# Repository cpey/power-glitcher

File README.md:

# Power Glitcher

Power glitcher circuit for voltage fault injection. Similar to [1], it includes
a DAC, a non-inverting amplification stage, and a push-pull follower output
circuit.

The board can function as ON/OFF switch, bypassing the DAC, by connecting a GPIO
output to the J5 connector and short-circuiting JP1. Refer to the
[schematic](https://github.com/cpey/power-glitcher/blob/main/power_glitcher/power_glitcher.pdf)
for more details.

[1] D. Oswald, *A Versatile Framework for Implementation Attacks on Cryptographic RFIDs and Embedded Devices*, 2010.

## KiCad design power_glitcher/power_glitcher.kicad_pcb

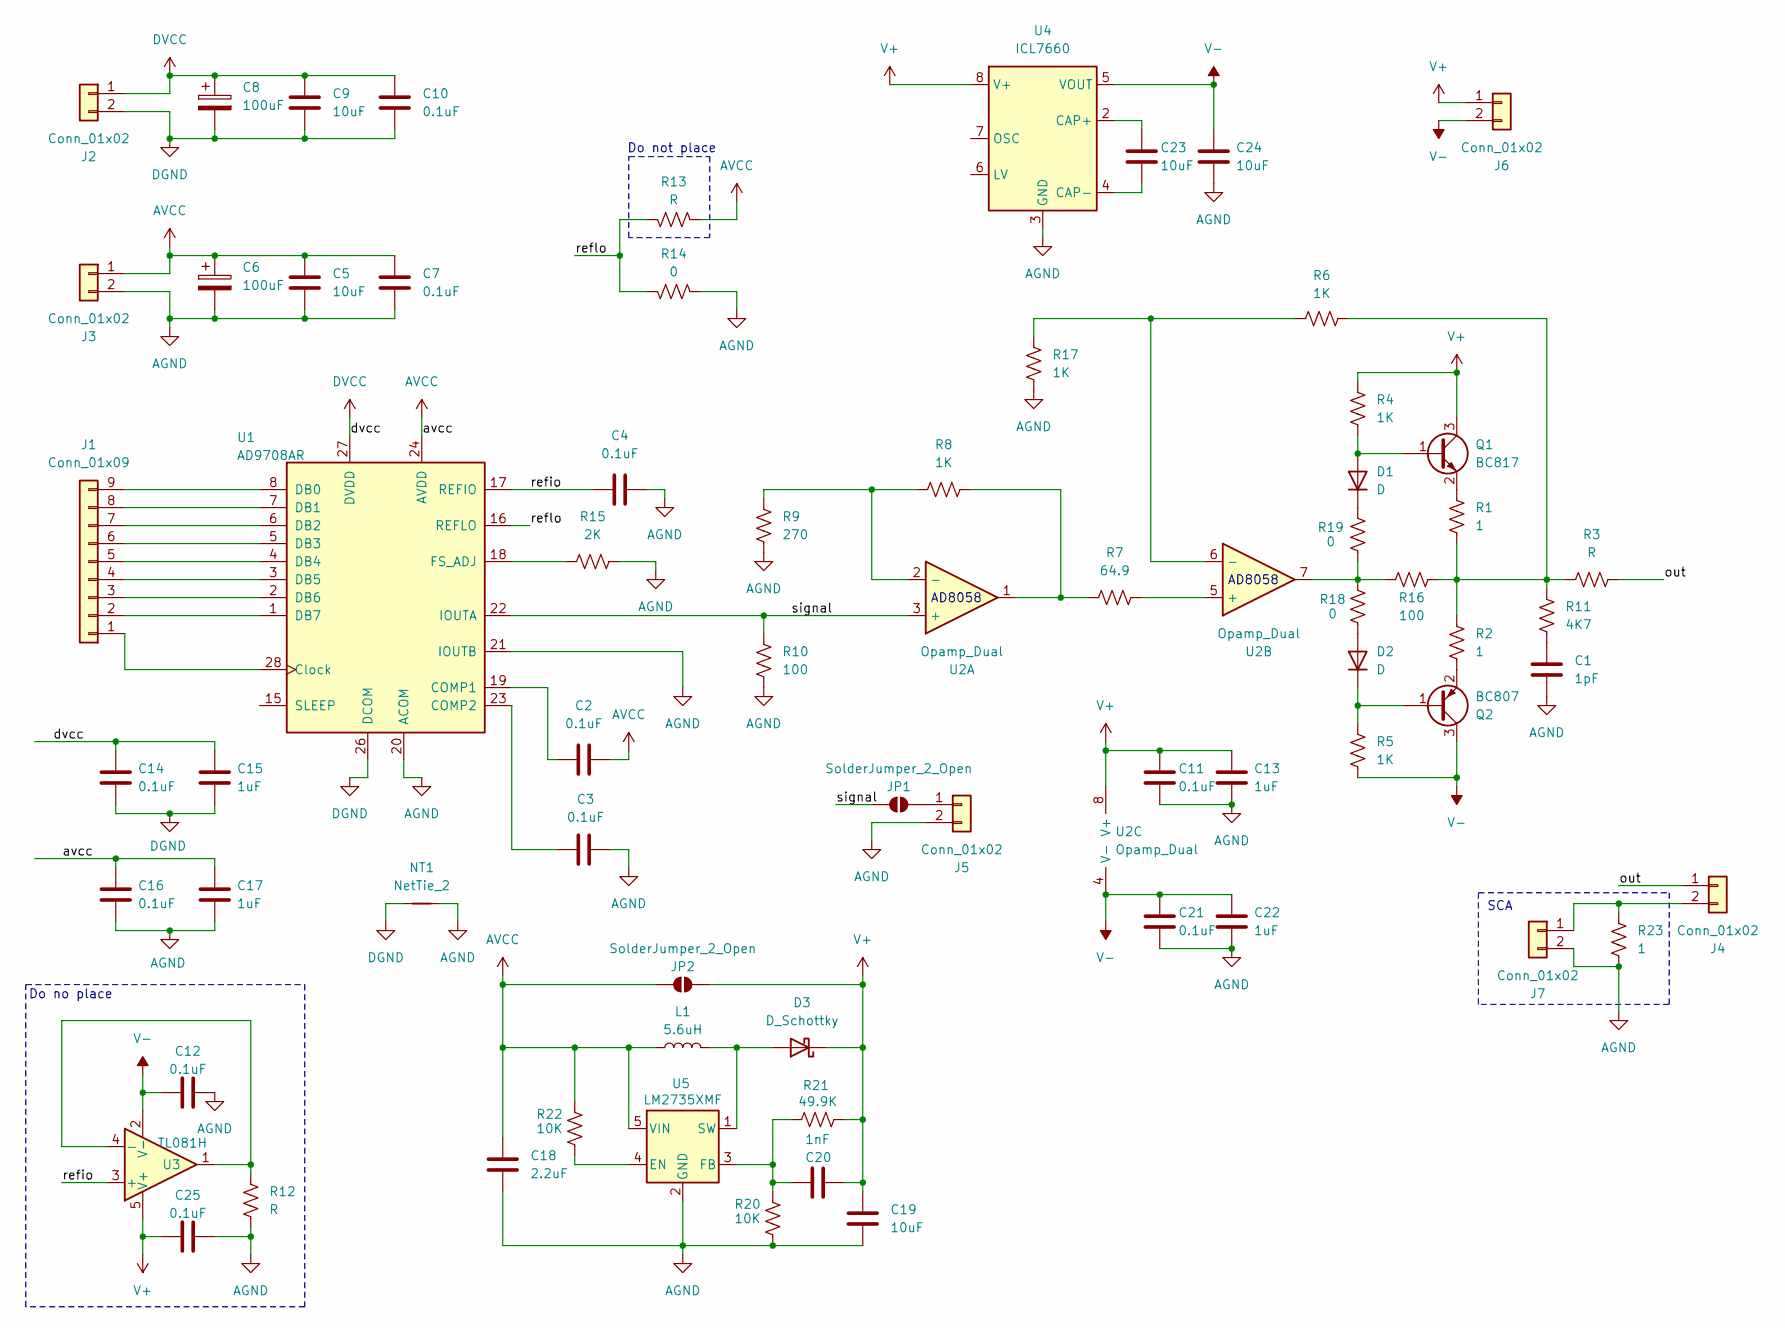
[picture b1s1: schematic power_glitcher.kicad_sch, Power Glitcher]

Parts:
C1: 1pF; C_0805_2012Metric
C2, C3, C4, C7, C10, C11, C12, C14, C16, C21, C25: 0.1uF; C_0805_2012Metric
C5, C9: 10uF; C_1210_3225Metric
C6, C8: 100uF; CP_Elec_6.3x5.8
C13, C15, C17, C22: 1uF; C_0805_2012Metric
C18: 2.2uF; C_0805_2012Metric
C19, C23, C24: 10uF; C_0805_2012Metric
C20: 1nF; C_0603_1608Metric
D1, D2: D; D_0805_2012Metric_Pad1.15x1.40mm_HandSolder
D3: D_Schottky; D_2114_3652Metric
J1: Conn_01x09; PinHeader_1x09_P2.54mm_Vertical
J2, J3, J4, J5, J6, J7: Conn_01x02; PinHeader_1x02_P2.54mm_Vertical
JP1, JP2: SolderJumper_2_Open; SolderJumper-2_P1.3mm_Open_Pad1.0x1.5mm
L1: 5.6uH; L_Vishay_IHLP-1616
NT1: NetTie_2; NetTie-2_SMD_Pad0.5mm
Q1: BC817; SOT-23
Q2: BC807; SOT-23
R1, R2, R23: 1; R_0805_2012Metric
R3, R12, R13: R; R_0805_2012Metric
R4, R5, R6, R8, R17: 1K; R_0805_2012Metric
R7: 64.9; R_0805_2012Metric
R9: 270; R_0805_2012Metric
R10, R16: 100; R_0805_2012Metric
R11: 4K7; R_0805_2012Metric
R14, R18, R19: 0; R_0805_2012Metric
R15: 2K; R_0805_2012Metric
R20, R22: 10K; R_0805_2012Metric
R21: 49.9K; R_0805_2012Metric
U1: AD9708AR; TSSOP-28_4.4x9.7mm_P0.65mm
U2: Opamp_Dual; SOIC-8_3.9x4.9mm_P1.27mm
U3: TL081H; SOT-23-5
U4: ICL7660; SO-8_3.9x4.9mm_P1.27mm
U5: LM2735XMF; SOT-23-5

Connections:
/out: J4.1, R3.2
/refio: C4.1, U1.17 (REFIO), U3.3 (+)
/reflo: R13.1, R14.1, U1.16 (REFLO)
/signal: JP1.2 (B), R10.2, U1.22 (IOUTA), U2.3 (+)
AGND: C1.2, C3.2, C4.2, C5.2, C6.2, C7.2, C11.2, C12.2, C13.2, C16.2, C17.2, C18.1, C19.1, C21.2, C22.2, C24.2, C25.1, J3.2, J5.2, J7.2, NT1.2, R9.1, R10.1, R12.1, R14.2, R15.1, R17.1, R20.1, R23.1, U1.20 (ACOM), U1.21 (IOUTB), U4.3 (GND), U5.2 (GND)
AVCC: C2.2, C5.1, C6.1, C7.1, C16.1, C17.1, C18.2, J3.1, JP2.2 (B), L1.1, R13.2, R22.2, U1.24 (AVDD), U5.5 (VIN)
DGND: C8.2, C9.2, C10.2, C14.2, C15.2, J2.2, NT1.1, U1.26 (DCOM)
DVCC: C8.1, C9.1, C10.1, C14.1, C15.1, J2.1, U1.27 (DVDD)
unnamed: C1.1, R11.1
unnamed: D1.2 (A), Q1.1 (B), R4.1
unnamed: D1.1 (K), R19.2
unnamed: D2.2 (A), R18.1
unnamed: D2.1 (K), Q2.1 (B), R5.2
unnamed: D3.2 (A), L1.2, U5.1 (SW)
unnamed: J1.1, U1.28 (Clock)
unnamed: J1.2, U1.1 (DB7)
unnamed: J1.3, U1.2 (DB6)
unnamed: J1.4, U1.3 (DB5)
unnamed: J1.5, U1.4 (DB4)
unnamed: J1.6, U1.5 (DB3)
unnamed: J1.7, U1.6 (DB2)
unnamed: J1.8, U1.7 (DB1)
unnamed: J1.9, U1.8 (DB0)
unnamed: J4.2, J7.1, R23.2
unnamed: J5.1, JP1.1 (A)
unnamed: Q1.2 (E), R1.1
unnamed: Q2.2 (E), R2.2
unnamed: R1.2, R2.1, R3.1, R6.2, R11.2, R16.2
unnamed: R7.1, R8.2, U2.1
unnamed: R16.1, R18.2, R19.1, U2.7
unnamed: C2.1, U1.19 (COMP1)
unnamed: C3.1, U1.23 (COMP2)
unnamed: R15.2, U1.18 (FS_ADJ)
unnamed: R8.1, R9.2, U2.2 (-)
unnamed: R7.2, U2.5 (+)
unnamed: R6.1, R17.2, U2.6 (-)
unnamed: R12.2, U3.1, U3.4 (-)
unnamed: C23.1, U4.2 (CAP+)
unnamed: C23.2, U4.4 (CAP-)
unnamed: R22.1, U5.4 (EN)
unnamed: C20.2, R20.2, R21.1, U5.3 (FB)
V+: C11.1, C13.1, C19.2, C20.1, C25.2, D3.1 (K), J6.1, JP2.1 (A), Q1.3 (C), R4.2, R21.2, U2.8 (V+), U3.5 (V+), U4.8 (V+)
V-: C12.1, C21.1, C22.1, C24.1, J6.2, Q2.3 (C), R5.1, U2.4 (V-), U3.2 (V-), U4.5 (VOUT)

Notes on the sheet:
AD8058
SCA
Do not place
Do no place

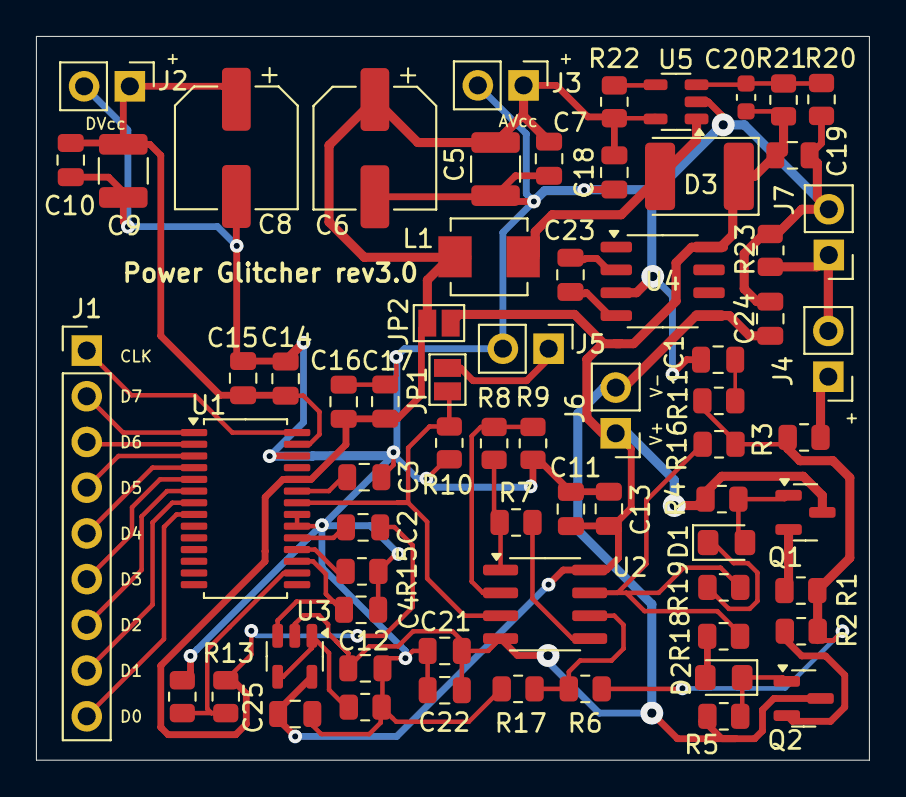
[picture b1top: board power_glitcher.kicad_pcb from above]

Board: 2 copper layers, 46.3 x 40.2 mm, 69 parts (1 on the bottom side), 43 nets.

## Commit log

2024-11-18 Rev 2.0
2024-11-24 Update BOM
2024-12-07 Extend README with ON/OFF setup mode
2024-12-09 Add bypass jumper for LM2735 and power analysis capability
